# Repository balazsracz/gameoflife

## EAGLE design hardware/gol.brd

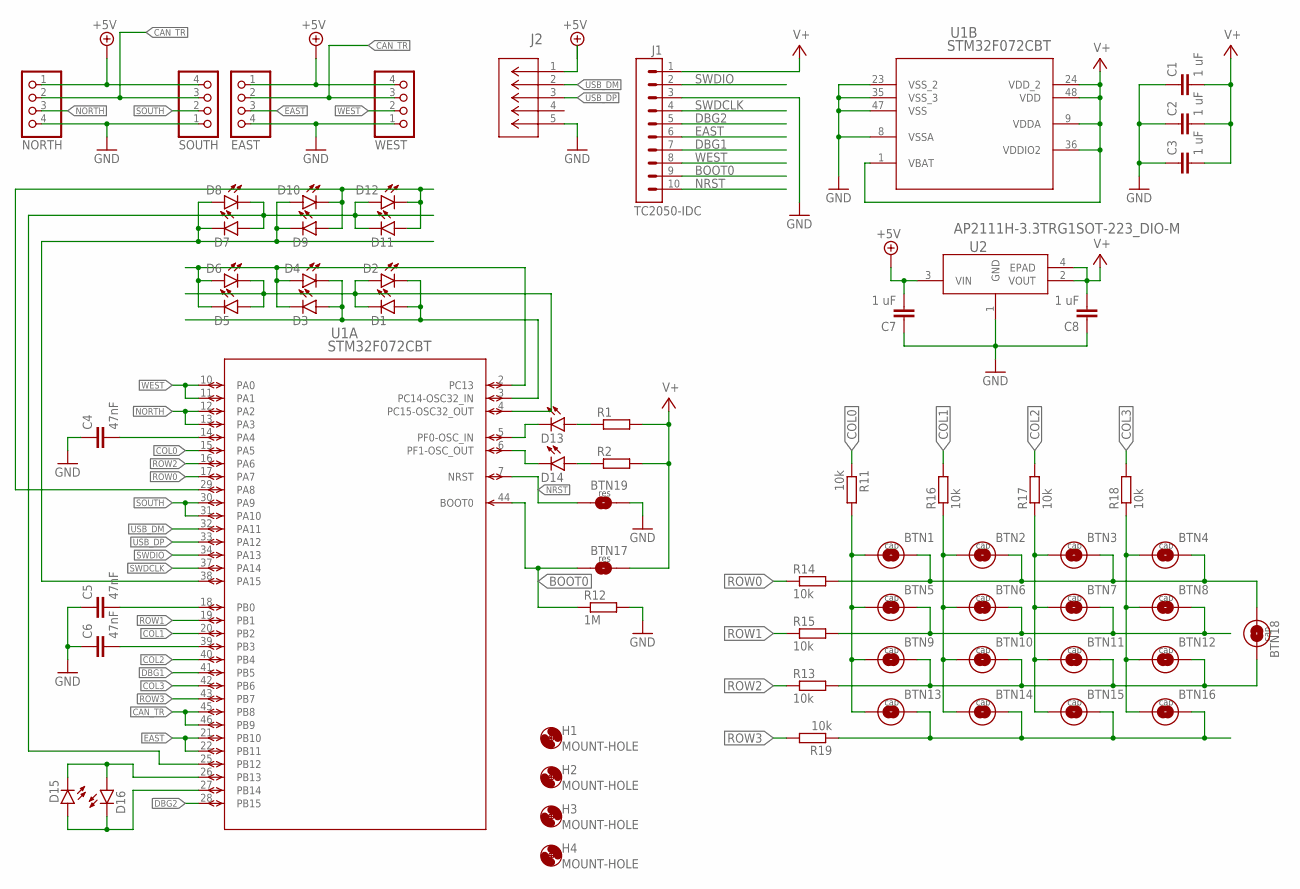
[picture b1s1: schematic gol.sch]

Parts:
BTN1: 1; COMB
BTN2: 2; COMB
BTN3: 3; COMB
BTN4: 4; COMB
BTN5: 5; COMB
BTN6: 6; COMB
BTN7: 7; COMB
BTN8: 8; COMB
BTN9: 9; COMB
BTN10: 10; COMB
BTN11: 11; COMB
BTN12: 12; COMB
BTN13: 13; COMB
BTN14: 14; COMB
BTN15: 15; COMB
BTN16: 16; COMB
BTN17: FLASH; COMB_EXPOSED
BTN18: MENU; COMB_NARROW
BTN19: RESET; COMB_EXPOSED
C1, C2, C3, C7, C8: 1 uF; C0603
C4, C5, C6: 47nF; C0603
D1, D2, D3, D4, D5, D6, D7, D8, D9, D10, D11, D12, D13, D14, D15, D16: LED-5MM; LED5MM
EAST: EAST; 1X04
H1, H2, H3, H4: MOUNT-HOLE; MOUNT-HOLE-2,8
J1: TC2050-IDC
J2: 2057-MCR-B-S-RA-TSMT-NP-CS4-T/RCT-ND; CONN_10118192-0002LF_AMP; DIGIKEY_PART_1 609-5379-1-ND
NORTH: NORTH; JP4-RA-FEM
R1, R2: R-EU-0207/8; 0207/8
R11, R13, R14, R15, R16, R17, R18, R19: 10k; R0603
R12: 1M; R0603
SOUTH: SOUTH; 1X04/90
U1: STM32F072CBT; LQFP48-7X7MM
U2: AP2111H-3.3TRG1SOT-223_DIO-M; SOT-223_DIO-M
WEST: WEST; 1X04

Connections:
+5V: C7.2, EAST.1, J2.1, NORTH.1, SOUTH.4, U2.3 (VIN), WEST.4
BOOT0: BTN17.P$1 (1), J1.9, R12.1, U1.44 (BOOT0)
CAN_TR: EAST.2, NORTH.2, SOUTH.3, U1.45 (PB8), U1.46 (PB9), WEST.3
COL0: R11.1, U1.15 (PA5)
COL1: R16.2, U1.20 (PB2)
COL2: R17.2, U1.40 (PB4)
COL3: R18.2, U1.42 (PB6)
DBG1: J1.7, U1.41 (PB5)
DBG2: J1.5, U1.28 (PB15)
EAST: EAST.3, J1.6, U1.21 (PB10), U1.22 (PB11)
GND: BTN19.P$2 (2), C1.1, C2.1, C3.1, C4.1, C5.1, C6.1, C7.1, C8.1, EAST.4, J1.3, J2.5, NORTH.4, R12.2, SOUTH.1, U1.8 (VSSA), U1.23 (VSS_2), U1.35 (VSS_3), U1.47 (VSS), U2.1 (GND), WEST.1
IN_COL0: BTN1.P$1 (1), BTN5.P$1 (1), BTN9.P$1 (1), BTN13.P$1 (1), R11.2
IN_COL1: BTN2.P$1 (1), BTN6.P$1 (1), BTN10.P$1 (1), BTN14.P$1 (1), R16.1
IN_COL2: BTN3.P$1 (1), BTN7.P$1 (1), BTN11.P$1 (1), BTN15.P$1 (1), R17.1
IN_COL3: BTN4.P$1 (1), BTN8.P$1 (1), BTN12.P$1 (1), BTN16.P$1 (1), R18.1
IN_ROW0: BTN1.P$2 (2), BTN2.P$2 (2), BTN3.P$2 (2), BTN4.P$2 (2), BTN18.P$1 (1), R14.2
IN_ROW1: BTN5.P$2 (2), BTN6.P$2 (2), BTN7.P$2 (2), BTN8.P$2 (2), R15.2
IN_ROW2: BTN9.P$2 (2), BTN10.P$2 (2), BTN11.P$2 (2), BTN12.P$2 (2), BTN18.P$2 (2), R13.2
IN_ROW3: BTN13.P$2 (2), BTN14.P$2 (2), BTN15.P$2 (2), BTN16.P$2 (2), R19.1
unnamed: C4.2, U1.14 (PA4)
unnamed: C5.2, U1.18 (PB0)
unnamed: C6.2, U1.39 (PB3)
unnamed: D13.A, R1.1
unnamed: D14.A, R2.1
NORTH: NORTH.3, U1.12 (PA2), U1.13 (PA3)
NRST: BTN19.P$1 (1), J1.10, U1.7 (NRST)
OUTA-L1: D3.K (C), D4.A, D5.K (C), D6.A, U1.2 (PC13)
OUTA-L2: D1.A, D2.K (C), D3.A, D4.K (C), U1.3 (PC14-OSC32_IN)
OUTA-L3: D1.K (C), D2.A, D5.A, D6.K (C), U1.4 (PC15-OSC32_OUT)
OUTB-L1: D7.K (C), D8.A, D9.K (C), D10.A, U1.38 (PA15)
OUTB-L2: D7.A, D8.K (C), D11.K (C), D12.A, U1.25 (PB12)
OUTB-L3: D9.A, D10.K (C), D11.A, D12.K (C), U1.29 (PA8)
OUTD13: D13.K (C), U1.5 (PF0-OSC_IN)
OUTD14: D14.K (C), U1.6 (PF1-OSC_OUT)
OUTD15: D15.K (C), D16.A, U1.26 (PB13)
OUTD16: D15.A, D16.K (C), U1.27 (PB14)
ROW0: R14.1, U1.17 (PA7)
ROW1: R15.1, U1.19 (PB1)
ROW2: R13.1, U1.16 (PA6)
ROW3: R19.2, U1.43 (PB7)
SOUTH: SOUTH.2, U1.30 (PA9), U1.31 (PA10)
SWDCLK: J1.4, U1.37 (PA14)
SWDIO: J1.2, U1.34 (PA13)
USB_DM: J2.2, U1.32 (PA11)
USB_DP: J2.3, U1.33 (PA12)
V+: BTN17.P$2 (2), C1.2, C2.2, C3.2, C8.2, J1.1, R1.2, R2.2, U1.1 (VBAT), U1.9 (VDDA), U1.24 (VDD_2), U1.36 (VDDIO2), U1.48 (VDD), U2.2 (VOUT), U2.4 (EPAD)
WEST: J1.8, U1.10 (PA0), U1.11 (PA1), WEST.2

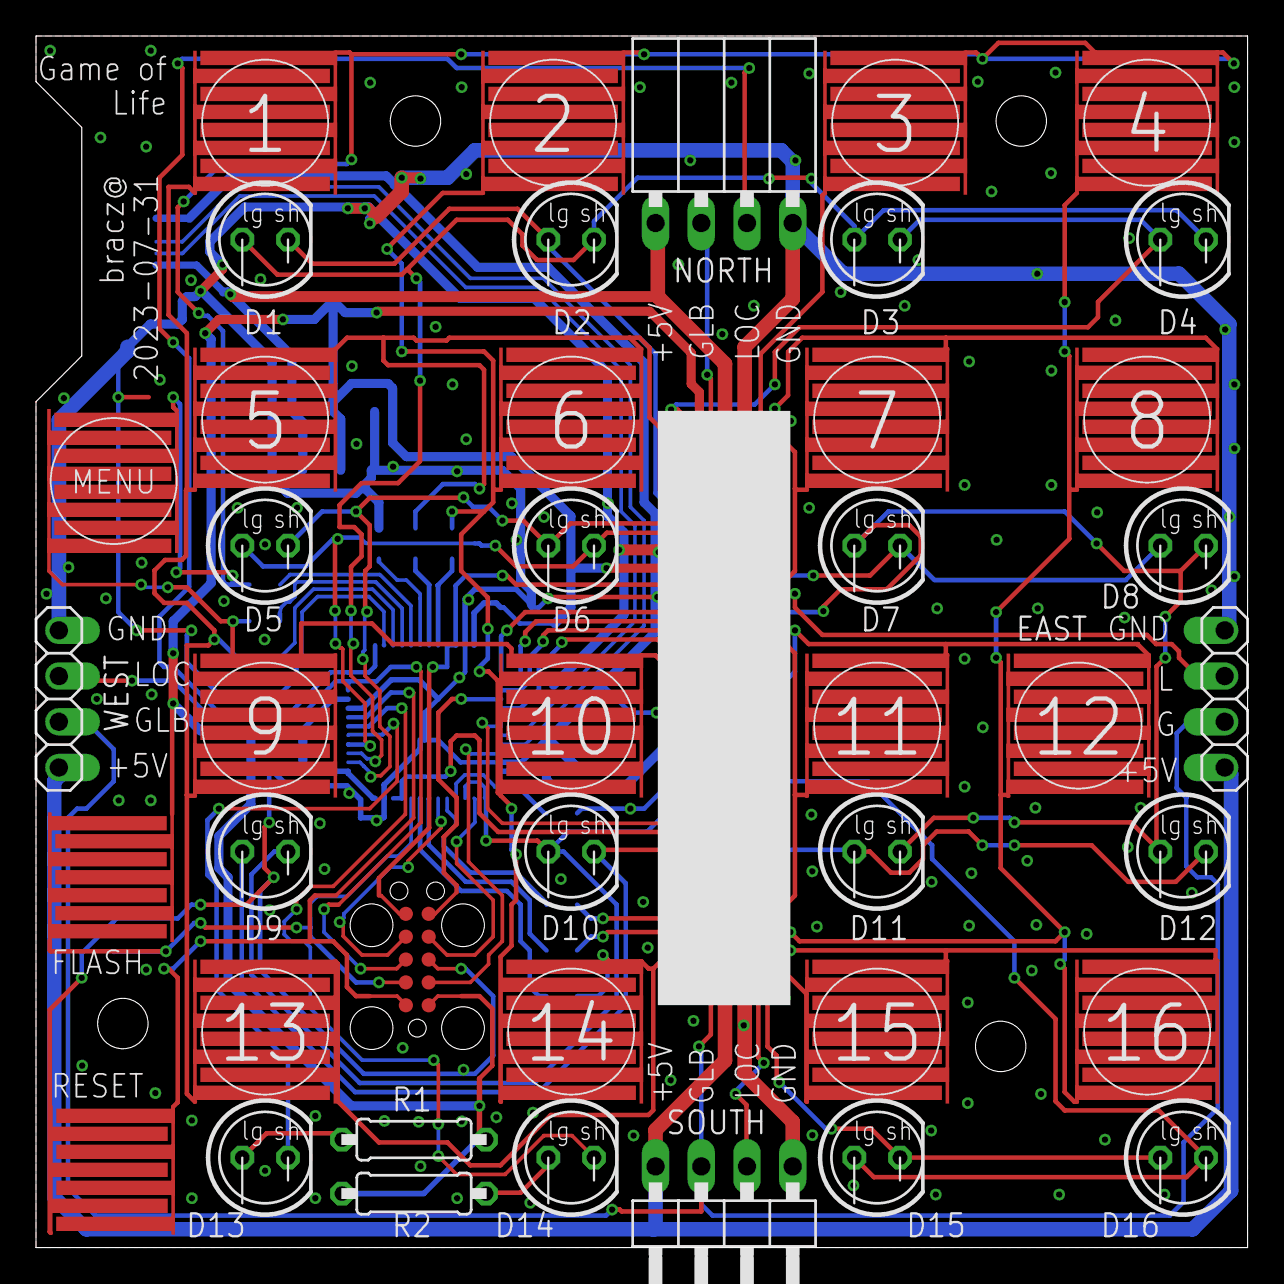
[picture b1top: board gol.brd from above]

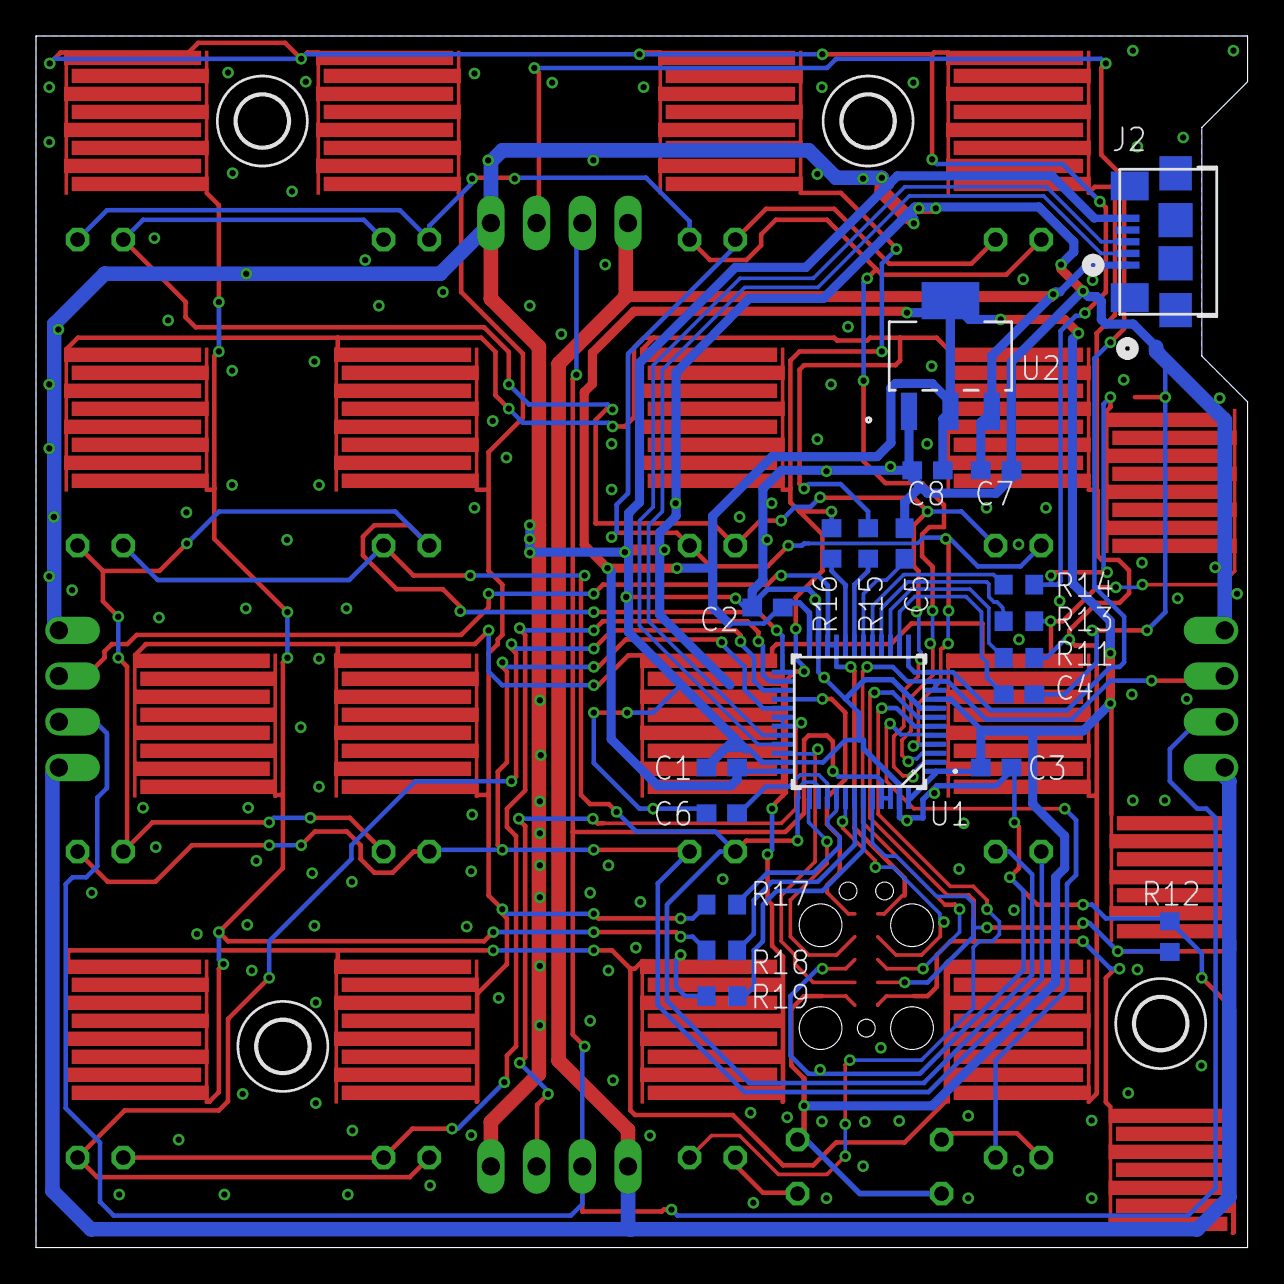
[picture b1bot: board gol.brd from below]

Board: 2 copper layers, 67.3 x 67.3 mm, 66 parts (24 on the bottom side), 47 nets.

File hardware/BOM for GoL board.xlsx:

Item # | *Designator | *Qty | Manufacturer | *Mfg Part # | Description / Value | *Package/Footprint | value | Type | Sub OK? | Your Instructions / Notes
1.0 | C1, C2, C3, C7, C8 | 5.0 | any | any | CAP CER 1UF 10V X5R 0603 +-20% | C0603 |  | SMD | Yes | Accepted substitution: X7R OK, higher voltage OK, tolerance +-20% +-10% or +-5%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
2.0 | R11, R13, R14, R15, R16, R17, R18, R19 | 8.0 | any | any | RES 10k OHM 0603 1/10W 5% | R0603 | 10k | SMD | Yes | Accepted substitution: 1% OK, higher wattage OK.
3.0 | J2 | 1.0 | Adam Tech | MCR-B-S-RA-TSMT-NP-CS4-T/R | MICRO USB, TYPE B, RIGHT ANGLE | micro usb | 2057-MCR-B-S-RA-TSMT-NP-CS4-T/RCT-ND | SMD | Yes | Digi-Key: 2057-MCR-B-S-RA-TSMT-NP-CS4-T/RCT-ND, example substitution: 609-5379-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
4.0 | R12 | 1.0 | any | any | RES 470k OHM 0603 1/10W 5% | R0603 | 470k | SMD | Yes | Accepted substitution: 1% OK, higher wattage OK. Values between 470k and 820k a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
5.0 | C4, C5, C6 | 3.0 | any | any | CAP CER 47nF 10V X5R 0603 +-10% | C0603 | 47nF | SMD | Yes | Accepted substitution: X7R OK, higher voltage OK, tolerance +-10% or +-5% OK.
6.0 | U2 | 1.0 | Diodes Incorporated | AP2111H-3.3TRG1 | Linear Voltage Regulator IC Positive Fixed 1 Output 600mA SOT-223-3 | SOT-223_DIO-M | AP2111H-3.3TRG1SOT-223_DIO-M | SMD | No | For a proposed substitution, contact me with part number.
7.0 | U1 | 1.0 | ST Microelectronics | STM32F072CBT | IC MCU 32BIT 128KB FLASH 48LQFP | LQFP48-7X7MM | STM32F072CBT | SMD | No
8.0 | BTN1,BTN2,BTN3,BTN4,BTN5,BTN6,BTN7,BTN8,BTN9,BTN10,BTN11,BTN12,BTN13,BTN14,BTN1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 |  |  |  |  |  |  | DNP |  | Do not populate

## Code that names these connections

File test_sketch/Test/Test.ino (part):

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#error must define one of HW_REV1 and HW_REV2.
#endif

static constexpr int LED13_PIN = PF0;
static constexpr int LED14_PIN = PF1;
//#ifdef HW_REV1
#if 1
static constexpr int LED15_PIN = PB13;
static constexpr int LED16_PIN = PB14;

static constexpr int MENU_PIN = PB15;
#endif

static constexpr int R1_PIN = PC14;
static constexpr int R2_PIN = PC15;
static constexpr int R3_PIN = PC13;

static constexpr int R4_PIN = PA15;
static constexpr int R5_PIN = PB12;
static constexpr int R6_PIN = PA8;

#ifdef HW_REV2
static constexpr int R15_PIN = PB13;
static constexpr int R16_PIN = PB14;
#endif

static constexpr int NORTH_TX_PIN = PA2;
static constexpr int NORTH_RX_PIN = PA3;
static constexpr int SOUTH_TX_PIN = PA9;
static constexpr int SOUTH_RX_PIN = PA10;
static constexpr int EAST_TX_PIN = PB10;
static constexpr int EAST_RX_PIN = PB11;
static constexpr int WEST_TX_PIN = PA0;
static constexpr int WEST_RX_PIN = PA1;

static constexpr int DBG2_PIN = PB15;
static constexpr int DBG1_PIN = PB5;


HardwareSerial serial_north(NORTH_RX_PIN, NORTH_TX_PIN);
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};

const CharlieProgram pg3[6] = {
  { R16_PIN, R15_PIN, DBG1_PIN, 14 },
  { R15_PIN, R16_PIN, DBG1_PIN, 15 },
  { DBG1_PIN, R16_PIN, R15_PIN, 16 },
  { DBG1_PIN, DBG1_PIN, R16_PIN, 16 },
  { DBG1_PIN, DBG1_PIN, DBG1_PIN, 16 },
  { DBG1_PIN, DBG1_PIN, DBG1_PIN, 16 },
};


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  //  pinMode(LED15_PIN, OUTPUT);
  //  pinMode(LED16_PIN, OUTPUT);

  pinMode(DBG1_PIN, INPUT);

#endif

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
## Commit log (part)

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2023-06-09 readme commit
2023-06-10 Adds library with custom parts. Adds most components to the schematic.
2023-06-11 Adds buttons and LEDs, adds schematic for grids.
2023-06-11 Adds micro-usb connector and 5V to 3V3 voltage regulator.
2023-06-19 Adds board layout file.
2023-06-19 Adds pinhead-2 side exit
2023-06-19 Completes layout of top side components. Adds +12V grid horizontally.
2023-06-19 Completes part of the layout and a small part of the routing around the MCU.
2023-06-20 Adds edge-of-board to the mini-usb connector. Routes the USB lines.
2023-06-20 more routing
2023-06-22 more routing work
2023-06-22 Prep for rearranging the capacitive inputs.
2023-06-22 Finishes rerouting the row/col ports
2023-06-22 more routing.
2023-06-23 Finishes routing most of the LEDs.
2023-06-23 Fixes routing of missing gnd lines.
2023-06-23 Adds 4-pin connector to east and west as well. Routes all remaining airwires.
2023-06-23 more labeling work. Updates parts so that they have outlines.
2023-06-23 Adds ground pour and vias.
2023-06-23 fills in an orphan
2023-06-23 adds right-angle female header. replaces north with this.
2023-06-23 Realigns the north connector with the edge. Updates some ground vias.
2023-06-23 Adds BOM export file.
2023-06-23 Adds processed BOM.
    Source:
    https://docs.google.com/spreadsheets/d/1hPsUb-Z08cYV5bmjL9kkSWupxSgmaA6F4GPnxTLXvis/edit#gid=1399560954
    Source:
    https://docs.google.com/spreadsheets/d/1w2xxuD-KHHd0Ks5WC5oyJ4qTA2DeoRDwIQumlcHQEdU/edit?resourcekey=0-Rwgz7ETt-QL0uQNMRU5OBQ#gid=1492933951
2023-06-23 Fixes DRC errors, approves false positives.
2023-06-23 Updates the mounting hole to take less floorspace.
    Adds four mounting holes to the device. Rearranges some wires and vias to make it work.
2023-06-23 Change author label.
2023-06-26 Adds gerber and assembly files for prototype run. Adds missing values for the pnp render. Adds a rendered pdf schematic.
2023-07-10 Adds example of how to use a hardware timer with the arduino API.
2023-07-10 Adds code that makes the touch sensing peripheral operational.
2023-07-15 Adds tests for the charlieplexing.
2023-07-17 Adds implementation to read all touch pads.
2023-07-17 Fork hardware/gol.sch to hardware/reva/gol.sch step 2
2023-07-17 Fork hardware/gol.sch to hardware/reva/gol.sch step 4
2023-07-17 Fork hardware/gol.brd to hardware/reva/gol.brd
2023-07-17 Fork hardware/gol.brd to hardware/reva/gol.brd step 2
2023-07-17 Fork hardware/gol.brd to hardware/reva/gol.brd step 4
2023-07-17 Adds reva schematic to the backup dir.
2023-07-17 Fork hardware/parts.lbr to hardware/reva/parts.lbr
2023-07-17 Fork hardware/parts.lbr to hardware/reva/parts.lbr step 4
2023-07-17 Moves the capacitive sensors from PB5-6 to PB6-7. Switches the debug output from PB7 to PB5.
2023-07-17 Replaces the menu button with capacitive option. Adds cirles and numbers to the capacitive buttons.
2023-07-17 Adds test code for serial sending and receiving on the local bus.
2023-07-17 Moves some labels so that they don't overlap with the cap buttons.
2023-07-18 Starts adding CAN initialization code.
2023-07-19 Makes the CAN-bus controller work.
2023-07-19 removes R1..R3 from one of the charlieplexing ranges.
2023-07-19 Removes R4-R6 for charlieplexing B.
2023-07-19 Moves D15/16 to a two-way charlieplexing.
2023-07-19 Layer visibility update.
2023-07-19 Moves some labels because they overlapped the part's pad.
2023-07-19 Moves the menu label into the circle.
2023-07-19 Updates visible label to not overlap button 1. Adds gerbers.
2023-07-21 Adds proper implementation of charlieplexing.
    Adds a minimal UI to test out a bunch of different LEDs.
2023-07-21 Fixes ghosting in the charlieplex handler.
2023-07-30 Updates schematic for rev 2.
2023-07-30 Updates the pin map for the touch channels on rev 2 board.
2023-07-30 Adds third channel of charlieplexing for D15 D16.
2023-07-30 Working rev 2 test sketch.
2023-07-31 Mirrors the holes to the bottom layer.
2023-07-31 Bump date code to 07-31
2023-07-31 Removes opening in soldermask and cream from the comb-resistive button footprint.
2023-07-31 Adds final gerbers and assembly file.
2023-07-31 Updates pads of the LQFP48 to be 11 mil wide instead of 12mil. The board house needs more clearance between pads.
2023-10-03 Adds rev C gerbers and BOM updates.
2023-10-03 Starts adding a production sketch.
2023-10-04 Adds example that blinks the two LEDs.
2023-10-04 Adds charlieplexing implementation. Fixes some bugs on the TCS peripehral driver.
2023-10-05 Updates PDF from latest schematic.
2023-10-05 Fixes correct operation of the touch controller. Apparently it depends on serial_east.begin(9600) call (???).
2023-10-05 Fixes real problem with the TSC: the gpio clock was not enabled.
2023-10-05 Adds local bus helper.
2023-10-05 Adds API declarations. Adds code for local bus GPIO API.
2023-10-06 Fixes local bus operation (especially east which was buggy).
2023-10-06 Cleans up dead and unneeded code.
2023-10-06 Fix comments and remove dead code.
2023-10-06 Adds global bus, a CAN driver and an example code exercising frame send and receive.
2023-10-06 Gets openlcb code to compile.
2023-10-06 Reformats global-bus. Ties it into the loop.
2023-10-07 Makes SendEvent use the actual alias allocated.
2023-10-09 Implements 200 msec delay between CID/RID.
2023-10-09 Fixes alias conflict handling a bit.
2023-10-10 Adds more constant definitions.
2023-10-10 Starts implementing the auto discovery.
2023-10-11 Cleanup the local variable names.
2023-10-11 Implements assignment of local coordinates.
2023-10-11 Implements some global commands. Adds supprot for reporting neighbors.
2023-10-11 Adds master election to the protocol engine.
2023-10-12 Adds a sketch to program IDs in to the MCU.
2023-10-13 Switches over the ID program code to work independently of USB and faster.
2023-10-13 Adds USB-CAN sketch.
2023-10-13 Adds tx and tx LEDs to the can-usb sketch.
2023-10-13 Fixes a nullptr dereference upon startup.
2023-10-13 Fix some race conditions with election.
2023-10-13 Rename terminology.
2023-10-13 fix bug in debunk.
2023-10-13 Fixes bug in TX busy.
2023-10-13 Makes the RX activity LED blink longer.
2023-10-13 Fixes in leader election code.
2023-10-13 Moves the leader election finish timeout to the regular timeout mechanism instead of the idle timeout.
2023-10-14 Implements a big part of the discovery leader.
2023-10-14 Fixes state machine of full discovery. Implements catchup discovery.
2023-10-15 Implements partial discovery in the new state machine. Cleans up some of the local state variables.
2023-10-15 Deletes dead code.
2023-10-15 Adds diagnoal neighbors to the direction table.
2023-10-15 Handles ReportNeighbors to discover who are the diagonal connections.
2023-10-15 Implements the global evolution tick in the leader.
2023-10-15 Adds actual iteration of the game on a single board.
    Adds remote control for
    - start, stop iteration
    - set random state
2023-10-15 Adds implementation of watching neighbor state. Fixes bug in remote start/stop iteration. It should only apply to a leader.
2023-10-16 Remove dead code.
2023-10-16 Remove some dead code.
2023-10-16 Simplifies the state machine since we can now enqueue events with correct loopback.
2023-10-16 Reduces latency of sending out events when the send queue is empty.
2023-10-16 Adds implementation of dead board detection.
2023-10-16 Adds include guards.
2023-10-16 Archives production sketch in a working form.
2023-10-16 Deletes all the implementation from the ProdSkeleton.
2023-10-25 rename prod sketch
2023-11-06 Adds support for entering bootloader mode from the prod sketch.
    Adds commands for broadcast firmware upgrade protocol.
2023-11-06 Fixes some bugs in the leader election protocol to make it more robust. Fixes bug in the dead plane detection. Only the leader should ever run the dead plane detection.
2023-11-12 Fixes hash aggregation of the global state.
2023-11-12 Adds a shellscript for bootloading through a USB-CAN adapter sketch.
2023-11-17 Makes it possible to run a single board alone.
    This is accomplished by looking for bus off condition on the CAN-bus,
    and canceling transmit frames after a msec when a bus off is detected.
2023-11-20 Reformats comments.
2023-11-20 Adds a mechanism to report the calibration data from the touch sensor.
2023-11-20 Adds a button combination to enter the bootloader via menu+16.
2023-11-20 Adds implementation of global menu functions. Adds a couple of debugging features.
2023-11-22 Fixes a bug that state overrides were not sending out state reports. This made the neighbors unaware that a state override has happened.
2023-11-22 Adds unit test framework and an example unittest.
2023-11-23 Adds unit tests to logic evolution.
2023-11-23 Adds more unittests, not run yet.
2023-11-23 Update skeleton code from prod.
2023-12-05 Disables tests on the prod sketch.
2023-12-05 Fixes bug when the stopped iteration was restarted and the tick timeout is in the past.
2023-12-05 Implements evolution speed menu buttons.
2023-12-05 Implements add random glider command. Formats protocol engine.
2023-12-06 Adds code for directional add glider calls.
2023-12-06 Adds implementation of neighbor debug command.
2023-12-07 Fixes bugs in clear and neighbor debug.
2023-12-07 Added czoccolo's implementation.
2023-12-07 Added czoccolo's implementation. (#1)
2023-12-10 Game of Life implementation from vdave@ (David Vago)
2023-12-11 Replaces menu blink with a full pattern that the engine can show on the leds.
2023-12-11 Lights up the master LEDs during discovery.
2023-12-11 Starts adding code for a second menu page.
2023-12-12 Makes only one of the two CAN pins have a pullup.
2023-12-12 Adds FindLeader command.
2023-12-12 Adds missing initialization to election start tick timeout.
2023-12-12 Fixes unwanted restarts after discovery.
2023-12-12 Implements display XY binary value request in prod.ino
2023-12-12 Makes the menu blinks blink dark as well, even if state is true for the given LED. Makes the second page menu blink double the speed.
2023-12-12 Update alias computation code so that alias happens to match the lowest byte of the node id.
2023-12-12 Implements second menu page and restructures menu items.
2023-12-12 Adds workarounds for infinite loops during startup. A full re-discover will not reinit all boards anymore. A local address conflict will overwrite the board's address instead of leaving the old addre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
2023-12-12 Game of Life implementation from vdave@ (David Vago) (#2)
2023-12-12 Move alternate prod sketches to standard name.
2023-12-12 Adds another command to stop all local outgoing signals.
2023-12-12 Fix bug when a node was added to the queue with address FFFF.
2023-12-12 Fix sketch main file names.
2023-12-12 Remove duplicate files.
2023-12-12 Replace duplicate files with symlinks.
2023-12-12 Fix compile error due to API change in the engine.
2023-12-12 Fixes a bug in CZ implementation. The State Set and State Or commands were executed indiscriminate of the target coordinates.
2023-12-12 Disables the bus off detection.
2023-12-12 Adds a stop local links command inbetween the discovery process.
2023-12-12 Fakes the neighbor array with x-y coordinates and deltas.
2023-12-13 Adds coordinate-based corner connections as well.
2023-12-13 Adds reboot script and address list.
2023-12-13 ignores neighbor reports.
2023-12-13 Reestablish two pullups per node.
2023-12-13 Optimize the CAN timing for short bus but high oscillator skew.
2023-12-13 Fixes conflict on firmware update complete vs report calibration. Updates the default iteration speed to 0.5 seconds.
2023-12-13 Adds reports to the leader job to debug failures in communication: - reports the number of nodes that checked in with state at each iteration - reports the number of times loop() got executed - repor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
2023-12-13 Adds address list text files.
2023-12-13 Adds osc test commands.
2024-01-29 Adds implementation for loading osc trim upon startup, and saving osc trim to nonvolatile storage when a given command asks us to do so.
2024-02-06 Center Trio

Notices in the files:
parts and their libraries:
COPYRIGHT: Copyright (C) 2023 Ultra Librarian. All rights reserved.
